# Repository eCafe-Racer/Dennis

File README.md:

# Dennis

Dennis is a part of the eCafe Racer project, a collaboration between Tim
LaGreca, Jordyn Brosemer, and Connor Winiarczyk where we are attempting to
build an electric racing motorcycle for fun and street cred.

The board serve's as both a controller for the bike's 12V digital signals
(such as its turn signals and brake lights), and also as a general interface
to the bike's CAN bus. We plan to use this interface both during development
for things like data acquisition and validation testing, as well as in the 
final product in order to provide features like control over bluetooth and
diagnostics.

## Design 

Dennis was originally designed as a carrier board for the Raspberry Pi
[Compute Module 4](https://www.raspberrypi.org/products/compute-module-4/?variant=raspberry-pi-cm4001000),
which aimed to integrate a complete embedded Linux system with the rest of the
circuitry, with peripherals controlled directly by the Pi's GPIO pins.
There were a number of issues with this approach, not the least of which was
that, as hobbyists, we lacked the equipment required to reliably solder the
CM4's high density connectors. There were some more subtle issues as well,
including that the high level of integration made our design much more
difficult to modify, and that the need to include integrated communication
interfaces for the pi increased both the size of the board and its complexity.

Our solution was simply to remove the Compute Module from the design, replacing
it with an ESP32 microcontroller. The microcontroller will be able to perform 
some simple logical control over the board, but its main job will be to provide
an interface to the board's peripherals over UART or USB, allowing a more
powerful computer to connect and perform higher level control and more
sophisticated analysis.  

In order to make interfacing with external computers easier, a 12 pin connector
(J1) was added to Dennis that exactly matches the pinout of the first 12
pins of the 40 pin connector on a traditional Raspberry Pi board. This allows
a Raspberry Pi to be mounted adjacent to Dennis in whatever enclosure it is 
being used in, and with a single ribbon cable, connect to the ESP's UART
interface, as well as the strapping pins needed to do firmware updates, the
board's I2C bus, and 5V power supply. These signals can also be controlled
over USB by way of an MCP2221A, giving us the flexibility to use other external
computers as well.

## Peripherals

Dennis has a 12V GPIO system with 7 digital outputs and 4 digital inputs.
Digital outputs can be set to either 12V (on), or High Impedance (off), meaning
they cannot sink current. The digital inputs consist of two "signal" inputs,
which measure voltage, and two "switch" inputs, which measure resistance to
ground. The switch inputs are meant to make it easier to install switches or
buttons on the bike and to program them for near arbitrary behavior, like
turn signals or a horn.

## Resources

- [Schematic](https://raw.githubusercontent.com/eCafe-Racer/Dennis/master/Documentation/0.2.1/schematic.pdf)
- [Step File](https://raw.githubusercontent.com/eCafe-Racer/Dennis/master/Documentation/0.2.1/step-file.step)
- [Gerbers](https://raw.githubusercontent.com/eCafe-Racer/Dennis/master/production/0.2/gerbers.zip)

- Top View

- Bottom View

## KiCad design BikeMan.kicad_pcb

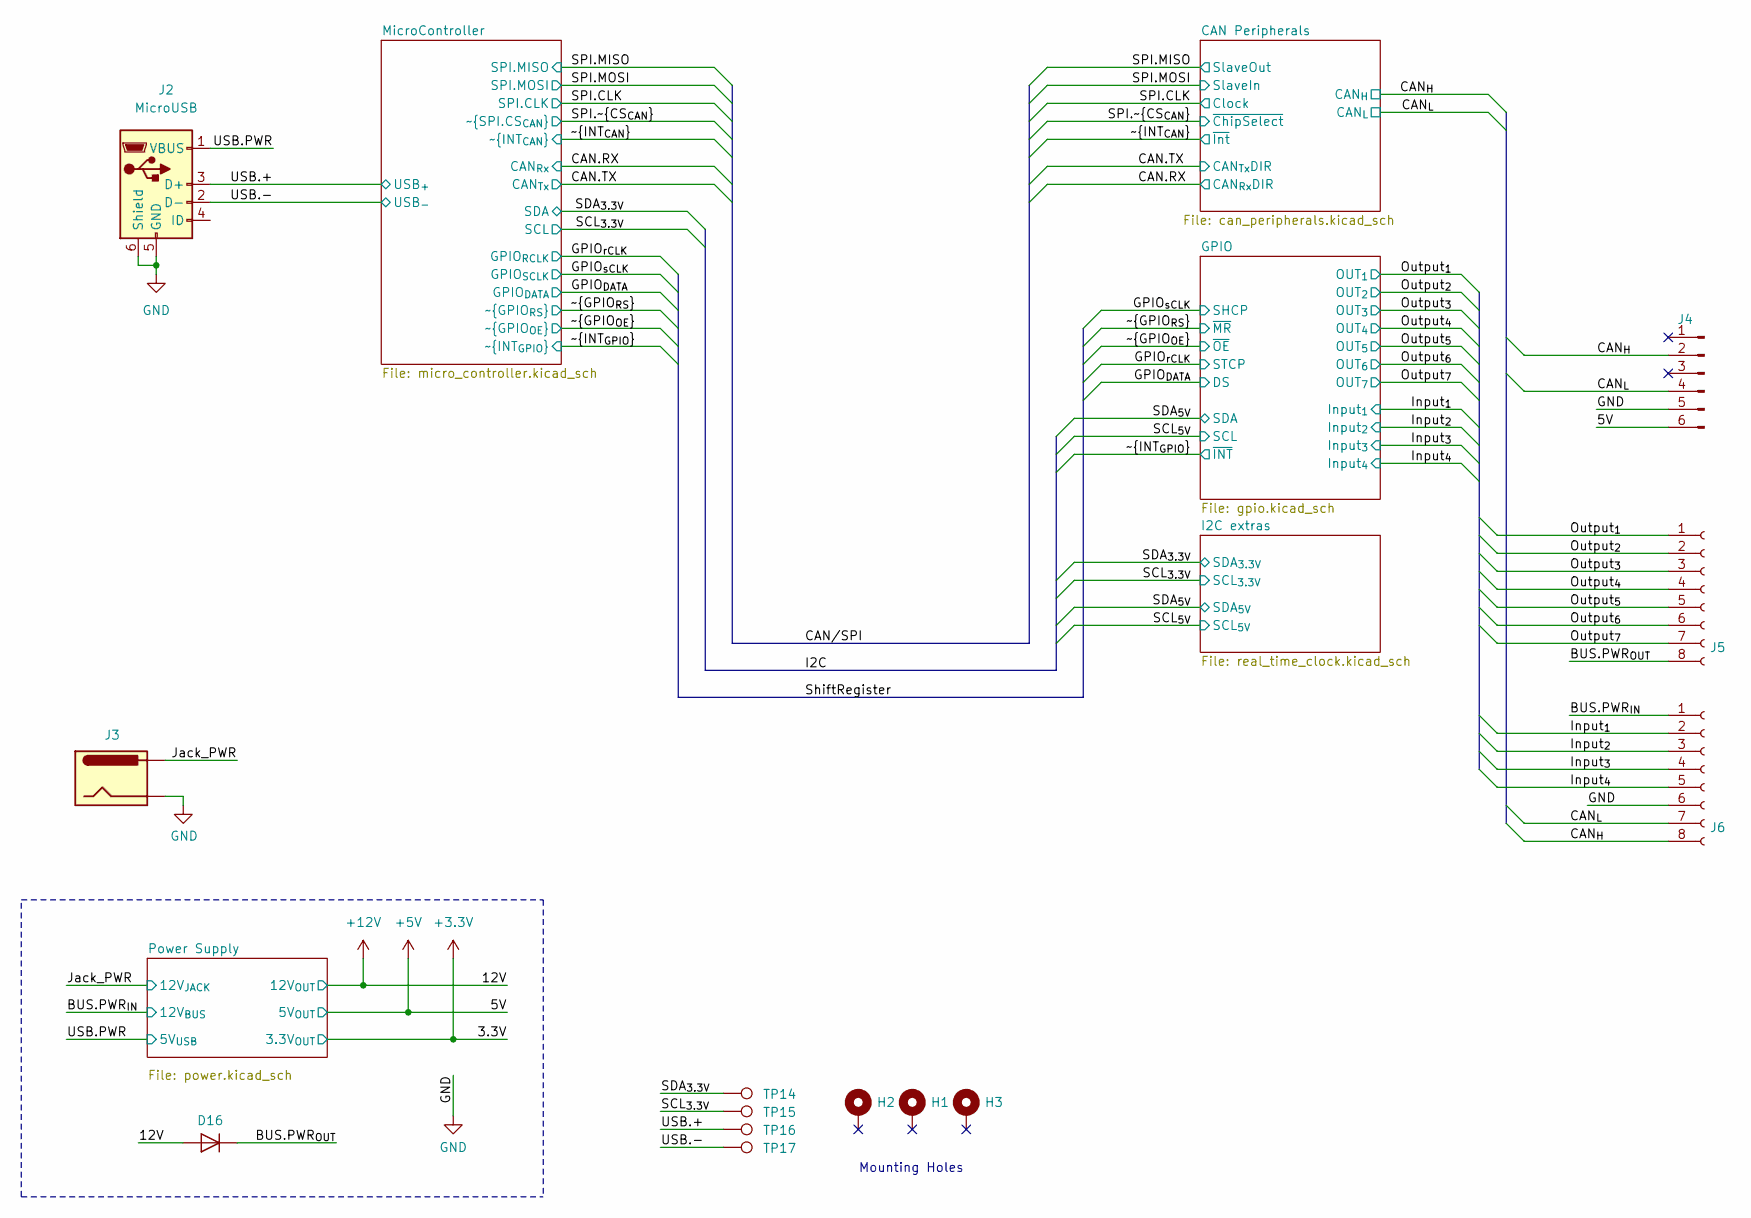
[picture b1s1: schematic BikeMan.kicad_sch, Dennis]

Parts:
D16: Diode; D_SOD-123F; Manufacturer Part NHP220SFT3G
H1, H2, H3: MountingHole_Pad; MountingHole_3.2mm_M3
J2: MicroUSB; USB_Micro-B_Amphenol_10104110_Horizontal; Manufacture Part 10118192-0002LF
J3: Barrel_Jack; BarrelJack_Horizontal; Manufacuturer Part 4840.2201
J4: Conn_01x06_Male; PinHeader_2x03_P2.54mm_Vertical
J5, J6: PushConnector_8pos; CUI_TBL004-508-08BE-2BE; Manufacturer Part TBL004-508-08BE-2GY
TP14, TP15, TP16, TP17: TestPoint; TestPoint_Pad_D1.5mm

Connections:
+5V: J4.6; also elsewhere on the board
+12V: D16.2 (A); also elsewhere on the board
/BUS.PWR_{IN}: J6.1; also elsewhere on the board
/BUS.PWR_{OUT}: D16.1 (K), J5.8
/CAN_{H}: J4.2, J6.8; also elsewhere on the board
/CAN_{L}: J4.4, J6.7; also elsewhere on the board
/Input_{1}: J6.2; also elsewhere on the board
/Input_{2}: J6.3; also elsewhere on the board
/Input_{3}: J6.4; also elsewhere on the board
/Input_{4}: J6.5; also elsewhere on the board
/Jack_PWR: J3.1; also elsewhere on the board
/Output_{1}: J5.1; also elsewhere on the board
/Output_{2}: J5.2; also elsewhere on the board
/Output_{3}: J5.3; also elsewhere on the board
/Output_{4}: J5.4; also elsewhere on the board
/Output_{5}: J5.5; also elsewhere on the board
/Output_{6}: J5.6; also elsewhere on the board
/Output_{7}: J5.7; also elsewhere on the board
/SCL_{3.3V}: TP15.1; also elsewhere on the board
/SDA_{3.3V}: TP14.1; also elsewhere on the board
/USB.+: J2.3 (D+), TP16.1; also elsewhere on the board
/USB.-: J2.2 (D-), TP17.1; also elsewhere on the board
/USB.PWR: J2.1 (VBUS); also elsewhere on the board
GND: J2.5 (GND), J2.6 (Shield), J3.2, J4.5, J6.6; also elsewhere on the board

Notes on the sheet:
Mounting Holes

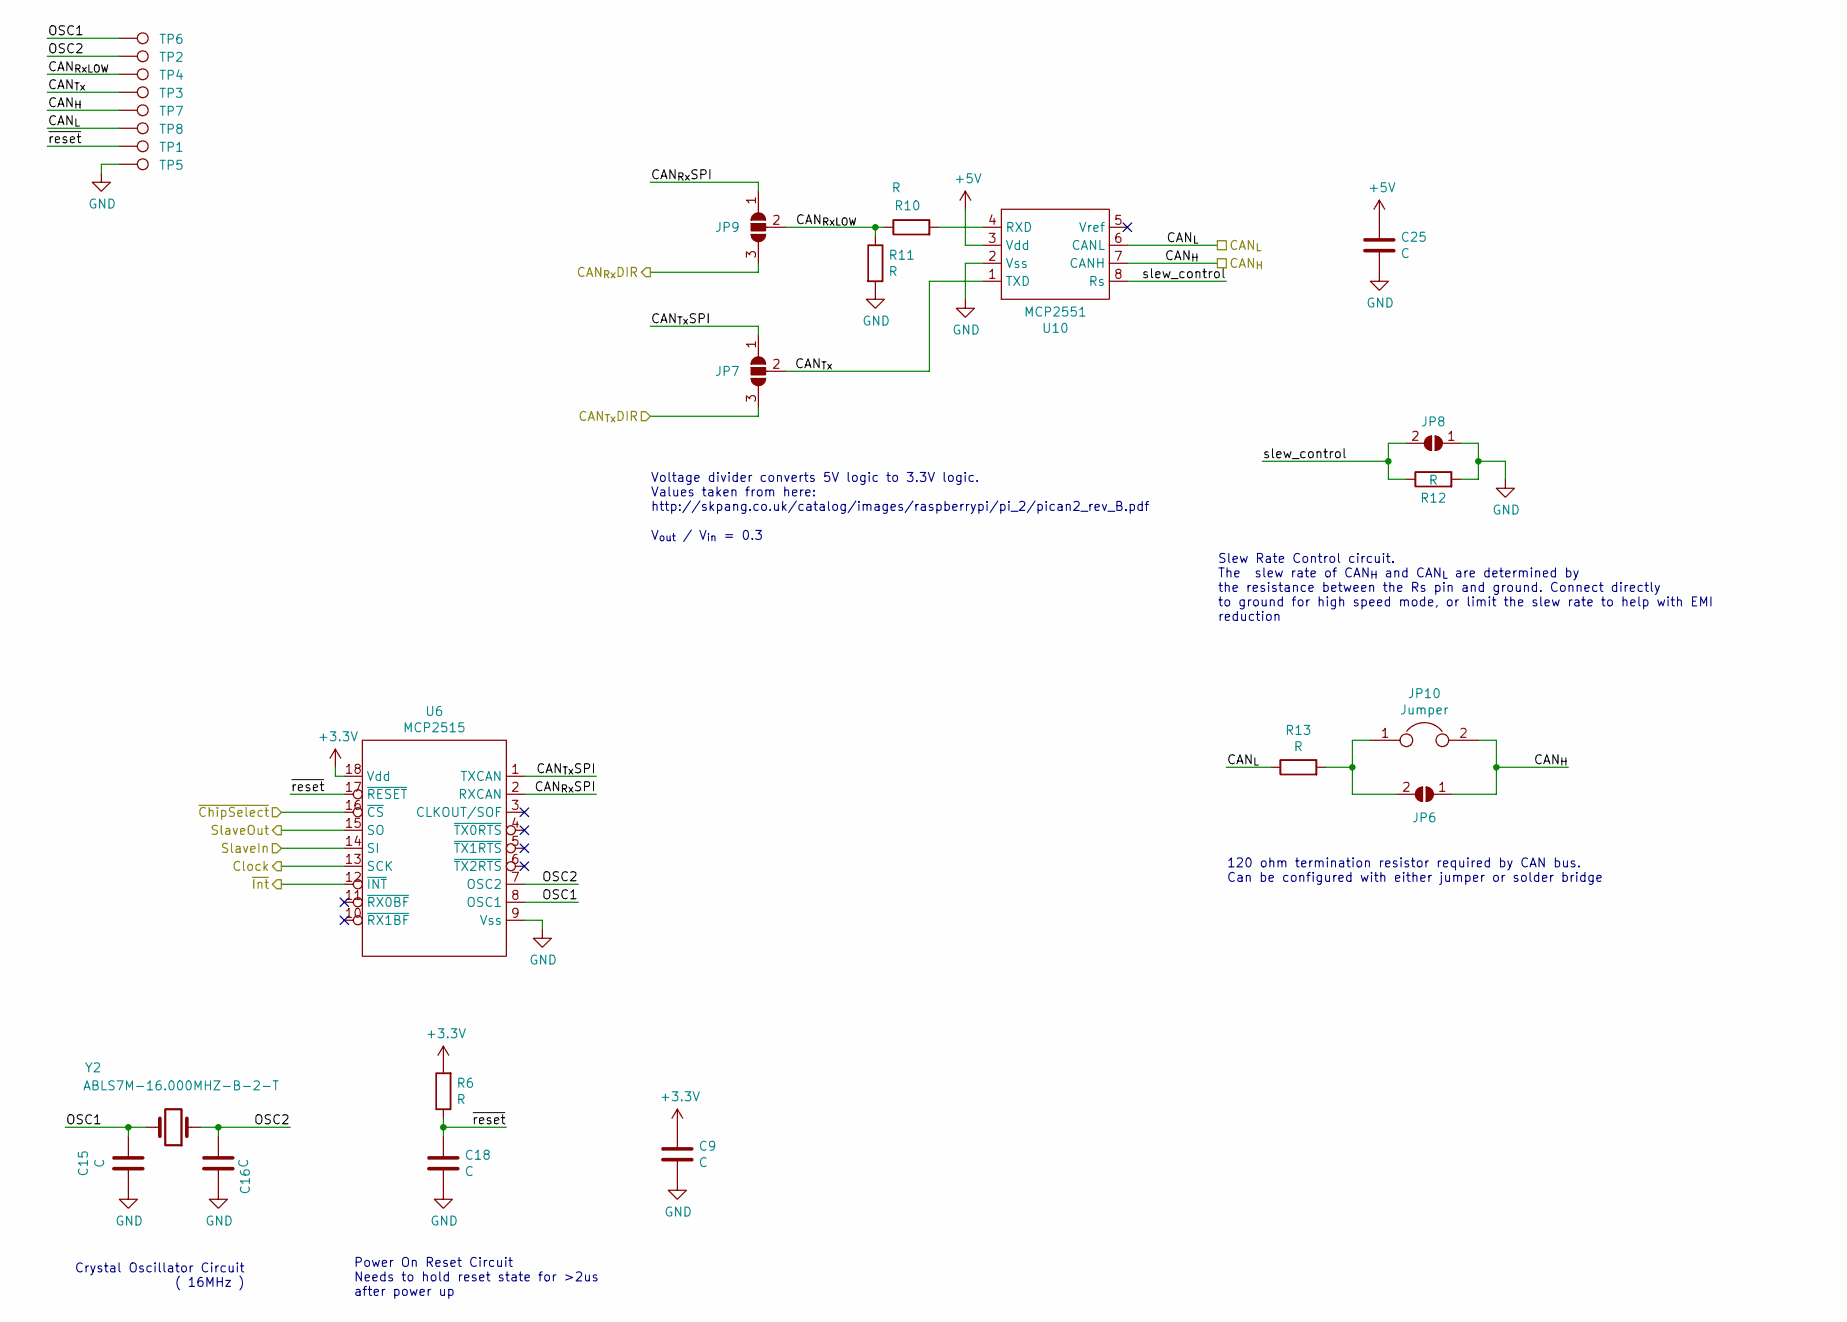
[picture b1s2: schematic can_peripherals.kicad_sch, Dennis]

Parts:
C9, C15, C16, C18, C25: C; C_0805_2012Metric
JP6, JP8: SolderJumper_2_Open; SolderJumper-2_P1.3mm_Open_RoundedPad1.0x1.5mm
JP7, JP9: SolderJumper_3_Open; SolderJumper-3_P1.3mm_Open_RoundedPad1.0x1.5mm_NumberLabels
JP10: Jumper; PinHeader_1x02_P2.54mm_Vertical
R6, R10, R11, R12, R13: R; R_0805_2012Metric
TP1, TP2, TP3, TP4, TP5, TP6, TP7, TP8: TestPoint; TestPoint_Pad_D1.5mm
U6: MCP2515; SOIC-18W_7.5x11.6mm_P1.27mm; Manufacturer Part MCP2515T-I/SO
U10: MCP2551; SO-8_3.9x4.9mm_P1.27mm; Manufacturer Part MCP2551T-E/SN
Y2: ABLS7M-16.000MHZ-B-2-T; Crystal-ABLS7M; Manufacturer Part ABLS7M-16.000MHZ-B-2-T

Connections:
+3V3: C9.1, R6.2, U6.18 (Vdd); also elsewhere on the board
+5V: C25.1, U10.3 (Vdd); also elsewhere on the board
/CAN Peripherals/CAN_{RxLOW}: JP9.2 (C), R10.1, R11.1, TP4.1
/CAN Peripherals/CAN_{Rx}SPI: JP9.1 (A), U6.2 (RXCAN)
/CAN Peripherals/CAN_{Tx}: JP7.2 (C), TP3.1, U10.1 (TXD)
/CAN Peripherals/CAN_{Tx}SPI: JP7.1 (A), U6.1 (TXCAN)
/CAN Peripherals/OSC1: C15.1, TP6.1, U6.8 (OSC1), Y2.2
/CAN Peripherals/OSC2: C16.1, TP2.1, U6.7 (OSC2), Y2.1
/CAN Peripherals/slew_control: JP8.2 (B), R12.1, U10.8 (Rs)
/CAN Peripherals/~reset: C18.1, R6.1, TP1.1, U6.17 (~RESET)
/CAN.RX: JP9.3 (B); also elsewhere on the board
/CAN.TX: JP7.3 (B); also elsewhere on the board
/CAN_{H}: JP6.1 (A), JP10.2, TP7.1, U10.7 (CANH); also elsewhere on the board
/CAN_{L}: R13.1, TP8.1, U10.6 (CANL); also elsewhere on the board
/SPI.CLK: U6.13 (SCK); also elsewhere on the board
/SPI.MISO: U6.15 (SO); also elsewhere on the board
/SPI.MOSI: U6.14 (SI); also elsewhere on the board
/SPI.~CS_{CAN}: U6.16 (~CS); also elsewhere on the board
/~INT_{CAN}: U6.12 (~INT); also elsewhere on the board
GND: C9.2, C15.2, C16.2, C18.2, C25.2, JP8.1 (A), R11.2, R12.2, TP5.1, U6.9 (Vss), U10.2 (Vss); also elsewhere on the board
unnamed: JP6.2 (B), JP10.1, R13.2
unnamed: R10.2, U10.4 (RXD)

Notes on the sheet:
Crystal Oscillator Circuit ( 16MHz )
Power On Reset Circuit Needs to hold reset state for >2us after power up
Voltage divider converts 5V logic to 3.3V logic. Values taken from here: http://skpang.co.uk/catalog/images/raspberrypi/pi_2/pican2_rev_B.pdf V_{out} / V_{in} = 0.3
Slew Rate Control circuit. The slew rate of CAN_{H} and CAN_{L} are determined by the resistance between the Rs pin and ground. Connect directly to ground for high speed mode, or limit the slew rate to help with EMI reduction
120 ohm termination resistor required by CAN bus. Can be configured with either jumper or solder bridge

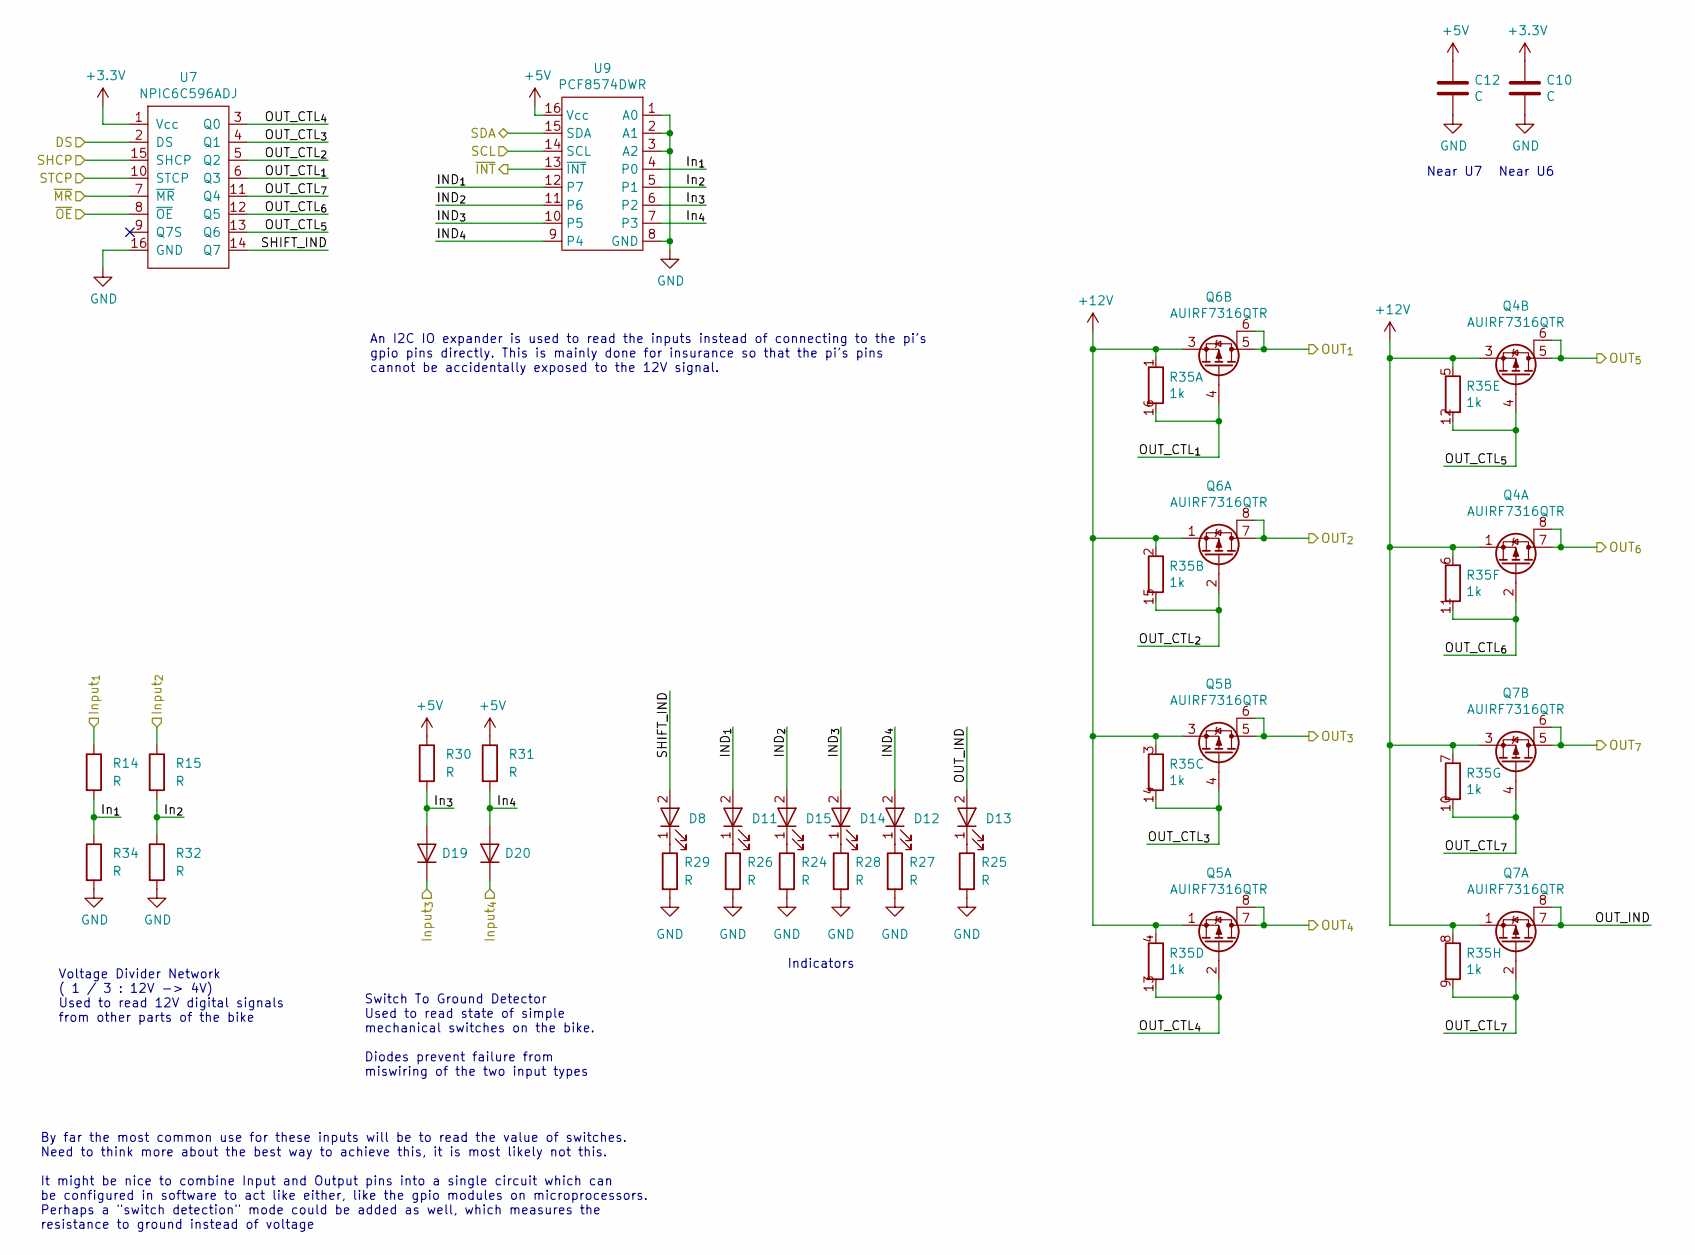
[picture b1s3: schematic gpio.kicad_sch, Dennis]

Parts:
C10, C12: C; C_0805_2012Metric
D8, D11, D12, D13, D14, D15: LED_Green; LED_0805_2012Metric_Pad1.15x1.40mm_HandSolder; Manufacturer Part CMD17-21VGC/TR8
D19, D20: Diode; D_SOD-123F; Manufacturer Part NHP220SFT3G
Q4, Q5, Q6, Q7: AUIRF7316QTR; SO-8_3.9x4.9mm_P1.27mm; Manufacturer Part AUIRF7316QTR
R14, R15, R24, R25, R26, R27, R28, R29, R30, R31, R32, R34: R; R_0805_2012Metric
R35: CTS-766161102GP; SOIC-16_3.9x9.9mm_P1.27mm; Manufacturer Part 766161102GP
U7: NPIC6C596ADJ; SOIC-16_4.55x10.3mm_P1.27mm; Manufacturer Part NPIC6C596ADJ
U9: PCF8574DWR; SOIC-16W_7.5x10.3mm_P1.27mm; Manufacturer Part PCF8574DWR

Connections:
+3V3: C10.1, U7.1 (Vcc); also elsewhere on the board
+5V: C12.1, R30.1, R31.1, U9.16 (Vcc); also elsewhere on the board
+12V: Q4.1 (S1), Q4.3 (S2), Q5.1 (S1), Q5.3 (S2), Q6.1 (S1), Q6.3 (S2), Q7.1 (S1), Q7.3 (S2), R35.1, R35.2, R35.3, R35.4, R35.5, R35.6, R35.7, R35.8; also elsewhere on the board
/GPIO/IND_{1}: D11.2, U9.12 (P7)
/GPIO/IND_{2}: D15.2, U9.11 (P6)
/GPIO/IND_{3}: D14.2, U9.10 (P5)
/GPIO/IND_{4}: D12.2, U9.9 (P4)
/GPIO/In_{1}: R14.2, R34.1, U9.4 (P0)
/GPIO/In_{2}: R15.2, R32.1, U9.5 (P1)
/GPIO/In_{3}: D19.2 (A), R30.2, U9.6 (P2)
/GPIO/In_{4}: D20.2 (A), R31.2, U9.7 (P3)
/GPIO/OUT_CTL_{1}: Q6.4 (G2), R35.16, U7.6 (Q3)
/GPIO/OUT_CTL_{2}: Q6.2 (G1), R35.15, U7.5 (Q2)
/GPIO/OUT_CTL_{3}: Q5.4 (G2), R35.14, U7.4 (Q1)
/GPIO/OUT_CTL_{4}: Q5.2 (G1), R35.13, U7.3 (Q0)
/GPIO/OUT_CTL_{5}: Q4.4 (G2), R35.12, U7.13 (Q6)
/GPIO/OUT_CTL_{6}: Q4.2 (G1), R35.11, U7.12 (Q5)
/GPIO/OUT_CTL_{7}: Q7.2 (G1), Q7.4 (G2), R35.9, R35.10, U7.11 (Q4)
/GPIO/OUT_IND: D13.2, Q7.7 (D1), Q7.8 (D1)
/GPIO/SHIFT_IND: D8.2, U7.14 (Q7)
/GPIO_{DATA}: U7.2 (DS); also elsewhere on the board
/GPIO_{rCLK}: U7.10 (STCP); also elsewhere on the board
/GPIO_{sCLK}: U7.15 (SHCP); also elsewhere on the board
/Input_{1}: R14.1; also elsewhere on the board
/Input_{2}: R15.1; also elsewhere on the board
/Input_{3}: D19.1 (K); also elsewhere on the board
/Input_{4}: D20.1 (K); also elsewhere on the board
/Output_{1}: Q6.5 (D2), Q6.6 (D2); also elsewhere on the board
/Output_{2}: Q6.7 (D1), Q6.8 (D1); also elsewhere on the board
/Output_{3}: Q5.5 (D2), Q5.6 (D2); also elsewhere on the board
/Output_{4}: Q5.7 (D1), Q5.8 (D1); also elsewhere on the board
/Output_{5}: Q4.5 (D2), Q4.6 (D2); also elsewhere on the board
/Output_{6}: Q4.7 (D1), Q4.8 (D1); also elsewhere on the board
/Output_{7}: Q7.5 (D2), Q7.6 (D2); also elsewhere on the board
/SCL_{5V}: U9.14 (SCL); also elsewhere on the board
/SDA_{5V}: U9.15 (SDA); also elsewhere on the board
/~GPIO_{OE}: U7.8 (~OE); also elsewhere on the board
/~GPIO_{RS}: U7.7 (~MR); also elsewhere on the board
/~INT_{GPIO}: U9.13 (~INT); also elsewhere on the board
GND: C10.2, C12.2, R24.2, R25.2, R26.2, R27.2, R28.2, R29.2, R32.2, R34.2, U7.16 (GND), U9.1 (A0), U9.2 (A1), U9.3 (A2), U9.8 (GND); also elsewhere on the board
unnamed: D8.1, R29.1
unnamed: D11.1, R26.1
unnamed: D12.1, R27.1
unnamed: D13.1, R25.1
unnamed: D14.1, R28.1
unnamed: D15.1, R24.1

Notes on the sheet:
By far the most common use for these inputs will be to read the value of switches. Need to think more about the best way to achieve this, it is most likely not this. It might be nice to combine Input and Output pins into a single circuit which can be configured in software to act like either, like 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
Voltage Divider Network ( 1 / 3 : 12V -> 4V) Used to read 12V digital signals from other parts of the bike
Switch To Ground Detector Used to read state of simple mechanical switches on the bike. Diodes prevent failure from miswiring of the two input types
An I2C IO expander is used to read the inputs instead of connecting to the pi's gpio pins directly. This is mainly done for insurance so that the pi's pins cannot be accidentally exposed to the 12V signal.
Indicators
Near U7
Near U6

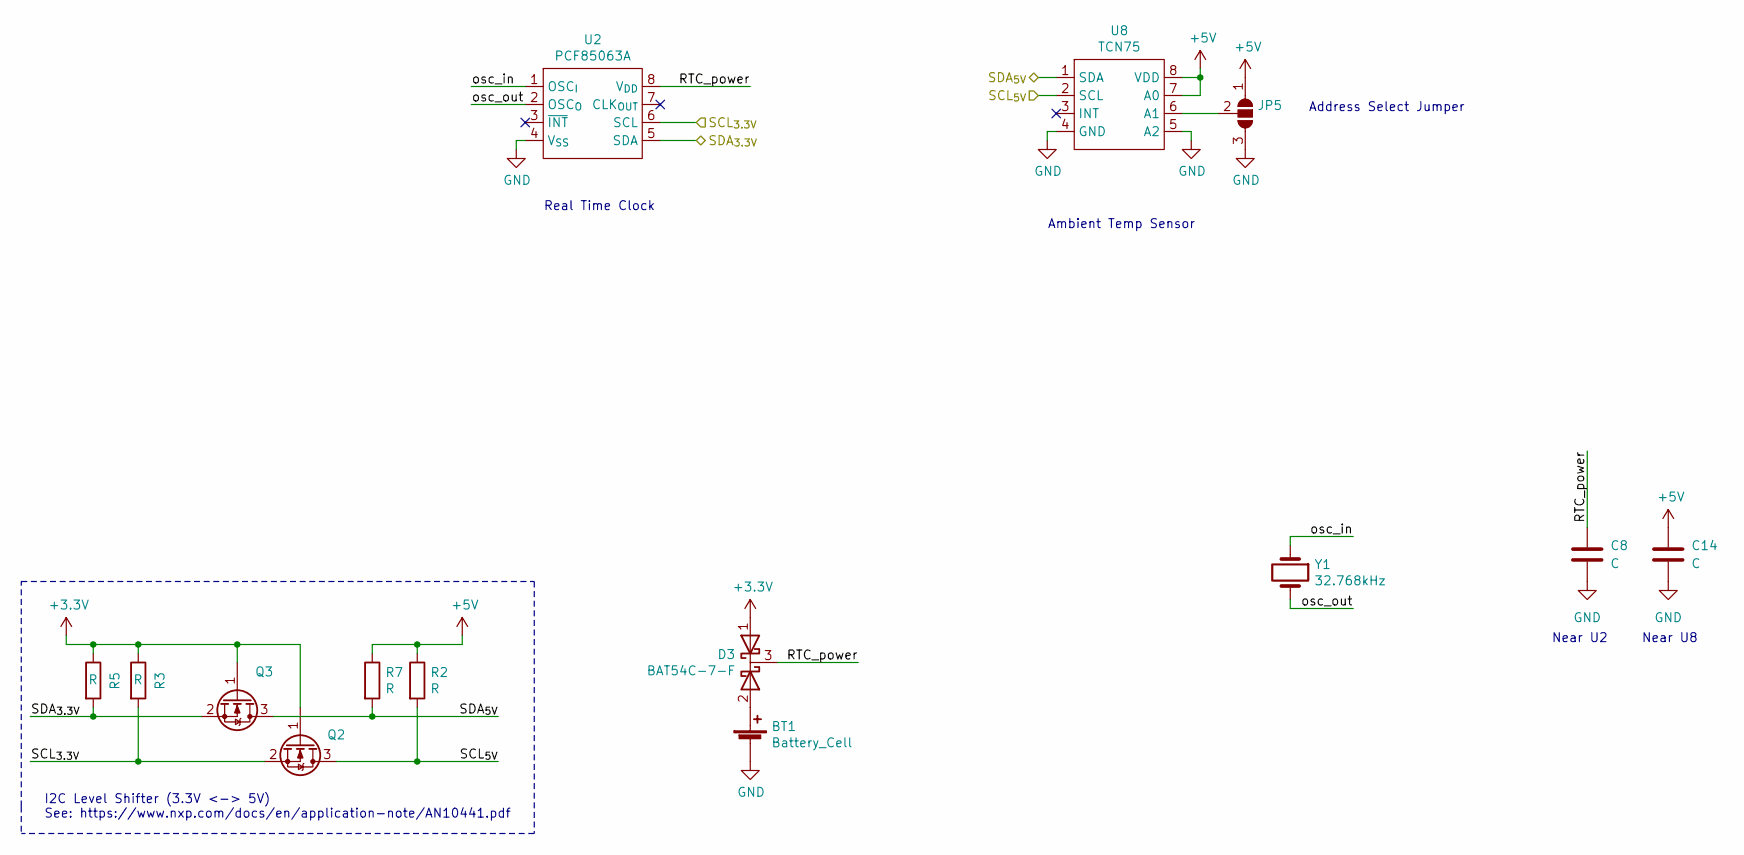
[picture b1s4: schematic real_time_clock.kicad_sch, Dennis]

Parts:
BT1: Battery_Cell; BatteryHolder_Keystone_3001_1x12mm; Manufacturer Part 3001
C8, C14: C; C_0805_2012Metric
D3: BAT54C-7-F; SOT-23; Manufacturer Part BAT54C-7-F
JP5: SolderJumper_3_Open; SolderJumper-3_P1.3mm_Open_RoundedPad1.0x1.5mm_NumberLabels
Q2, Q3: DMN62D0U-7; SOT-23; Manufacturer Part DMN62D0U-7
R2, R3, R5, R7: R; R_0805_2012Metric
U2: PCF85063A; SOIC-8_3.9x4.9mm_P1.27mm; Manufacturer Part PCF85063AT/AY
U8: TCN75; SOIC-8_3.9x4.9mm_P1.27mm; Supply Voltage 5.0V; Manufacturer Part TCN75-5.0MOA
Y1: Crystal-CM7V-T1A-32.768kHz; Crystal-CM7V; Manufacturer Part CM7V-T1A-32.768KHZ-6PF-20PPM-TB-QA

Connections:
+3V3: D3.1 (Anode_{1}), Q2.1 (G), Q3.1 (G), R3.1, R5.1; also elsewhere on the board
+5V: C14.1, JP5.1 (A), R2.1, R7.1, U8.7 (A0), U8.8 (VDD); also elsewhere on the board
/I2C extras/RTC_power: C8.1, D3.3 (Cathode), U2.8 (V_{DD})
/I2C extras/osc_in: U2.1 (OSC_{I}), Y1.1
/I2C extras/osc_out: U2.2 (OSC_{O}), Y1.2
/SCL_{3.3V}: Q2.2 (S), R3.2, U2.6 (SCL); also elsewhere on the board
/SCL_{5V}: Q2.3 (D), R2.2, U8.2 (SCL); also elsewhere on the board
/SDA_{3.3V}: Q3.2 (S), R5.2, U2.5 (SDA); also elsewhere on the board
/SDA_{5V}: Q3.3 (D), R7.2, U8.1 (SDA); also elsewhere on the board
GND: BT1.2 (-), C8.2, C14.2, JP5.3 (B), U2.4 (V_{SS}), U8.4 (GND), U8.5 (A2); also elsewhere on the board
unnamed: BT1.1 (+), D3.2 (Anode_{2})
unnamed: JP5.2 (C), U8.6 (A1)

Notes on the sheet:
I2C Level Shifter (3.3V <-> 5V) See: https://www.nxp.com/docs/en/application-note/AN10441.pdf
Real Time Clock
Ambient Temp Sensor
Address Select Jumper
Near U2
Near U8

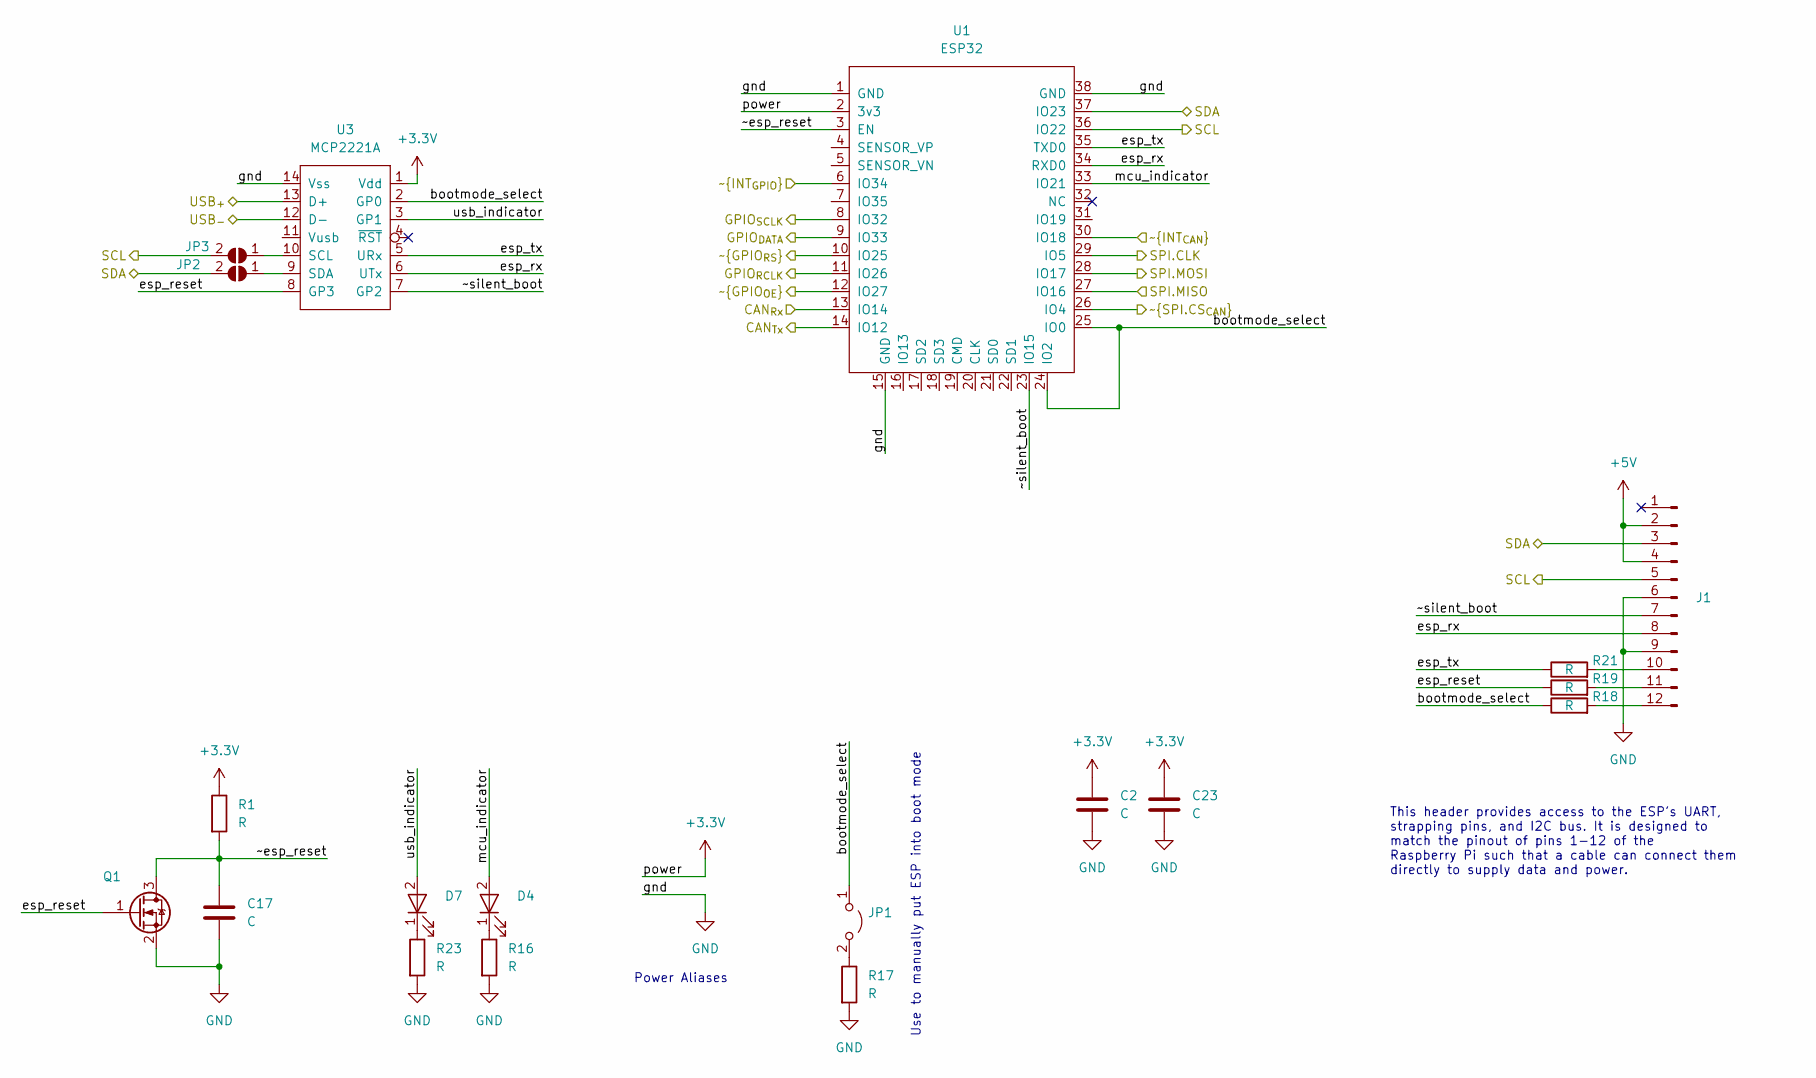
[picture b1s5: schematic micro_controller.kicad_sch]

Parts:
C2, C17, C23: C; C_0805_2012Metric
D4, D7: LED_Green; LED_0805_2012Metric_Pad1.15x1.40mm_HandSolder; Manufacturer Part CMD17-21VGC/TR8
J1: Conn_01x12_Male; PinHeader_2x06_P2.54mm_Vertical
JP1: Jumper_2_Open; PinHeader_1x02_P2.54mm_Vertical
JP2, JP3: SolderJumper_2_Open; SolderJumper-2_P1.3mm_Open_RoundedPad1.0x1.5mm
Q1: DMN62D0U-7; SOT-23; Manufacturer Part DMN62D0U-7
R1, R16, R17, R18, R19, R21, R23: R; R_0805_2012Metric
U1: ESP32; MODULE_ESP32-WROOM-32; Manufacturer Part ESP32-WROOM-32
U3: MCP2221A; TSSOP-14_4.4x5mm_P0.65mm; Manufacturer Part MCP2221AT-I/ST

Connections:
+3V3: C2.1, C23.1, R1.1, U1.2 (3v3), U3.1 (Vdd); also elsewhere on the board
+5V: J1.2, J1.4; also elsewhere on the board
/CAN.RX: U1.13 (IO14); also elsewhere on the board
/CAN.TX: U1.14 (IO12); also elsewhere on the board
/GPIO_{DATA}: U1.9 (IO33); also elsewhere on the board
/GPIO_{rCLK}: U1.11 (IO26); also elsewhere on the board
/GPIO_{sCLK}: U1.8 (IO32); also elsewhere on the board
/MicroController/bootmode_select: JP1.1 (A), R18.1, U1.24 (IO2), U1.25 (IO0), U3.2 (GP0)
/MicroController/esp_reset: Q1.1 (G), R19.1, U3.8 (GP3)
/MicroController/esp_rx: J1.8, U1.34 (RXD0), U3.6 (UTx)
/MicroController/esp_tx: R21.1, U1.35 (TXD0), U3.5 (URx)
/MicroController/mcu_indicator: D4.2, U1.33 (IO21)
/MicroController/usb_indicator: D7.2, U3.3 (GP1)
/MicroController/~esp_reset: C17.1, Q1.3 (D), R1.2, U1.3 (EN)
/MicroController/~silent_boot: J1.7, U1.23 (IO15), U3.7 (GP2)
/SCL_{3.3V}: J1.5, JP3.2 (B), U1.36 (IO22); also elsewhere on the board
/SDA_{3.3V}: J1.3, JP2.2 (B), U1.37 (IO23); also elsewhere on the board
/SPI.CLK: U1.29 (IO5); also elsewhere on the board
/SPI.MISO: U1.27 (IO16); also elsewhere on the board
/SPI.MOSI: U1.28 (IO17); also elsewhere on the board
/SPI.~CS_{CAN}: U1.26 (IO4); also elsewhere on the board
/USB.+: U3.13 (D+); also elsewhere on the board
/USB.-: U3.12 (D-); also elsewhere on the board
/~GPIO_{OE}: U1.12 (IO27); also elsewhere on the board
/~GPIO_{RS}: U1.10 (IO25); also elsewhere on the board
/~INT_{CAN}: U1.30 (IO18); also elsewhere on the board
/~INT_{GPIO}: U1.6 (IO34); also elsewhere on the board
GND: C2.2, C17.2, C23.2, J1.6, J1.9, Q1.2 (S), R16.2, R17.2, R23.2, U1.1 (GND), U1.15 (GND), U1.38 (GND), U3.14 (Vss); also elsewhere on the board
unnamed: D4.1, R16.1
unnamed: D7.1, R23.1
unnamed: J1.10, R21.2
unnamed: J1.11, R19.2
unnamed: J1.12, R18.2
unnamed: JP1.2 (B), R17.1
unnamed: JP2.1 (A), U3.9 (SDA)
unnamed: JP3.1 (A), U3.10 (SCL)

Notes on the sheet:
Power Aliases
Use to manually put ESP into boot mode
This header provides access to the ESP's UART, strapping pins, and I2C bus. It is designed to match the pinout of pins 1-12 of the Raspberry Pi such that a cable can connect them directly to supply data and power.

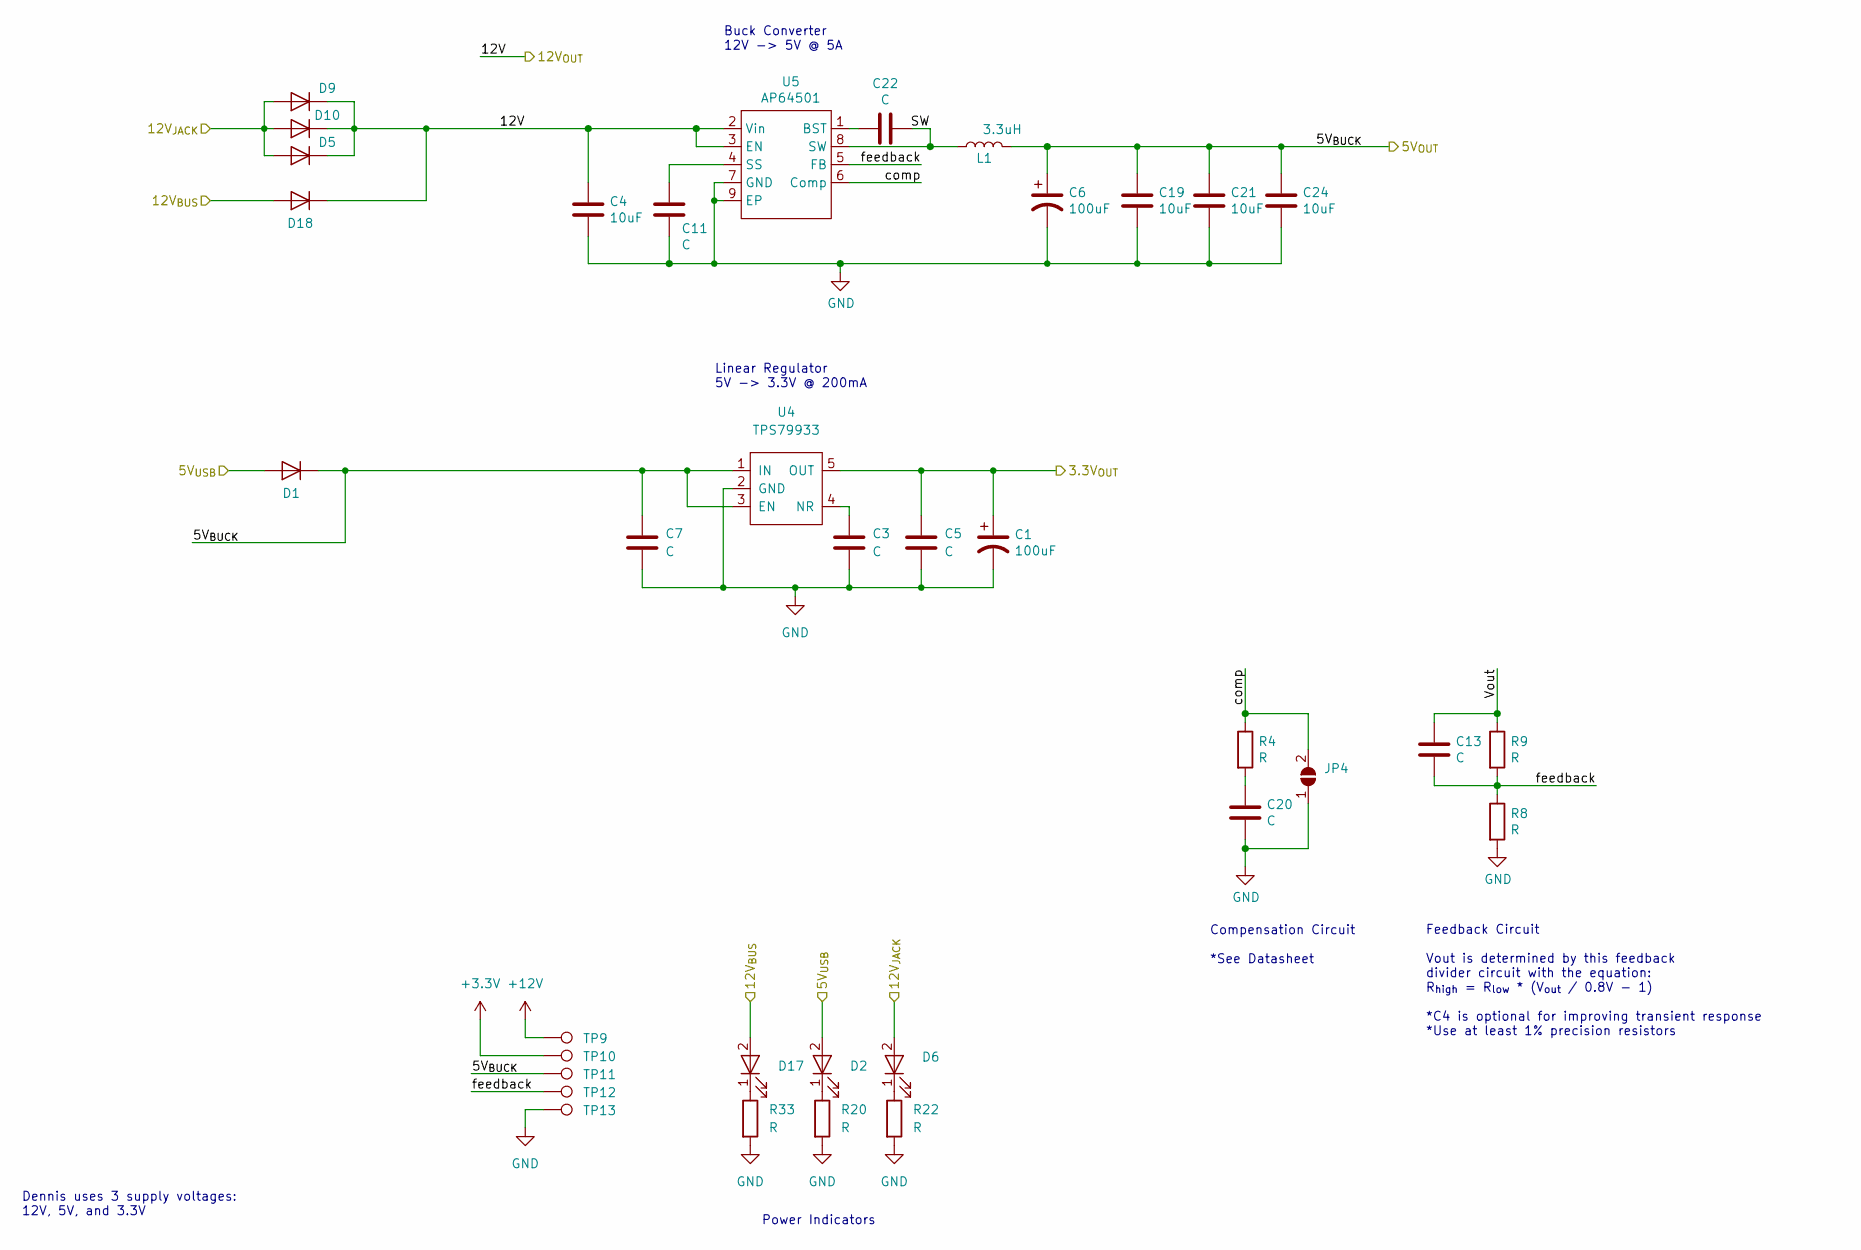
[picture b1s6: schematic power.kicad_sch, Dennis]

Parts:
C1, C6: 100uF; CP_Elec_6.3x5.9; Voltage 25V; Manufacturer Part A768EB107M1ELAS036
C3, C5, C7, C11, C13, C20, C22: C; C_0805_2012Metric
C4, C19, C21, C24: 10uF; C_0805_2012Metric; Voltage Rating 16V; Tolerance 20%; Manufacturer Part C2012X5R1C106K085AC
D1, D5, D9, D10, D18: Diode; D_SOD-123F; Manufacturer Part NHP220SFT3G
D2, D6, D17: LED_Green; LED_0805_2012Metric_Pad1.15x1.40mm_HandSolder; Manufacturer Part CMD17-21VGC/TR8
JP4: SolderJumper_2_Open; SolderJumper-2_P1.3mm_Open_RoundedPad1.0x1.5mm
L1: 3.3uH; Bourns SRN6045Y Inductor; Manufacturer Part SRN6045TA-3R3Y
R4, R8, R9, R20, R22, R33: R; R_0805_2012Metric
TP9, TP10, TP11, TP12, TP13: TestPoint; TestPoint_Pad_D1.5mm
U4: TPS79933; SOT-23-5; Manufacturer Part TPS79933DDCR
U5: AP64501; SOIC-8-1EP_3.9x4.9mm_P1.27mm_EP2.514x3.2mm; Manufacturer Part AP64501SP-13

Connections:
+3V3: C1.1, C5.1, TP10.1, U4.5 (OUT); also elsewhere on the board
+5V: C6.1, C7.1, C19.1, C21.1, C24.1, D1.1 (K), L1.2, TP11.1, U4.1 (IN), U4.3 (EN); also elsewhere on the board
+12V: C4.1, D5.1 (K), D9.1 (K), D10.1 (K), D18.1 (K), TP9.1, U5.2 (Vin), U5.3 (EN); also elsewhere on the board
/BUS.PWR_{IN}: D17.2, D18.2 (A); also elsewhere on the board
/Jack_PWR: D5.2 (A), D6.2, D9.2 (A), D10.2 (A); also elsewhere on the board
/Power Supply/SW: C22.2, L1.1, U5.8 (SW)
/Power Supply/Vout: C13.1, R9.1
/Power Supply/comp: JP4.2 (B), R4.1, U5.6 (Comp)
/Power Supply/feedback: C13.2, R8.1, R9.2, TP12.1, U5.5 (FB)
/USB.PWR: D1.2 (A), D2.2; also elsewhere on the board
GND: C1.2, C3.2, C4.2, C5.2, C6.2, C7.2, C11.2, C19.2, C20.2, C21.2, C24.2, JP4.1 (A), R8.2, R20.2, R22.2, R33.2, TP13.1, U4.2 (GND), U5.7 (GND), U5.9 (EP); also elsewhere on the board
unnamed: C3.1, U4.4 (NR)
unnamed: C11.1, U5.4 (SS)
unnamed: C20.1, R4.2
unnamed: C22.1, U5.1 (BST)
unnamed: D2.1, R20.1
unnamed: D6.1, R22.1
unnamed: D17.1, R33.1

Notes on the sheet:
Dennis uses 3 supply voltages: 12V, 5V, and 3.3V
Linear Regulator 5V -> 3.3V @ 200mA
Buck Converter 12V -> 5V @ 5A
Power Indicators
Compensation Circuit *See Datasheet
Feedback Circuit Vout is determined by this feedback divider circuit with the equation: R_{high} = R_{low} * (V_{out} / 0.8V - 1) *C4 is optional for improving transient response *Use at least 1% precision resistors
